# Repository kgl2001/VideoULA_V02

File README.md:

# VideoULA V02 — BBC Micro Video ULA Replacement
## 64-pin Xilinx XC9572XL CPLD Version

This repository contains the hardware design and firmware for the VideoULA V02, a drop-in replacement for the VC2069 Video ULA (IC6) in the Acorn BBC Micro Model B and Master 128.

---

## Project Overview

The original BBC Micro Video ULA (IC6) is a custom ASIC that is no longer manufactured. Failed or missing ULAs result in a non-functional machine. This project provides a modern replacement using a CPLD and a small external SRAM for palette storage.

There are three hardware versions of this replacement, each in a separate repository:

| Version | CPLD | Macrocells | Tool | Repository |
|---|---|---|---|---|
| V01 | Xilinx XC9572XL-10-VQ44 | 72 | ISE 14.7 | [VideoULA_V01](https://github.com/kgl2001/VideoULA_V01) |
| **V02** | Xilinx XC9572XL-10-VQ64 | 72 | ISE 14.7 | This repo |
| V03 | Atmel ATF1504AS-10AU44 | 64 | Quartus 13.0 SP1 | [VideoULA_V03](https://github.com/kgl2001/VideoULA_V03) |

All three versions share the same 28-pin DIP footprint as the original ULA and are pin-compatible with the BBC Micro motherboard.

---

## V02 Hardware

- **CPLD**: Xilinx XC9572XL-10-VQ64 (72 macrocells, 3.3V core, 5V tolerant I/O)
- **SRAM**: ISSI IS61LV256AL-10TLI (32K×8, 3.3V, TSOP-28, 10ns) — only locations 0-15 and bits 0-3 used
- **Oscillator**: 48MHz SMD oscillator (3225 package, 3.3V)
- **LDO**: XC6206P332MR (SOT-23, 3.3V) — powers CPLD core, oscillator and clock buffer
- **Clock buffer**: 74LV6T17 — buffers all 5 clock outputs (8/4/2/1MHz, CRTC) for Master 128 compatibility (5V powered); 6th channel buffers the 16MHz clock input
- **Power selection**: Solder bridge selects 3.3V or 5V for SRAM supply

### Key improvements over V01

- 64-pin CPLD package — more I/O pins available
- All clock outputs buffered via 74LV6T17 — improved compatibility with Master 128 custom ICs which require higher logic 1 voltage
- 3.3V SRAM option (IS61LV256AL-10TLI, 10ns) — faster and runs from 3.3V rail
- 3.3V oscillator — reduces CPLD input clamping current and heat
- 74LV6T17 used for both clock output buffering and 16MHz CLK_IN conditioning (Schmitt trigger)
- Separate CLK_16M and CLK_48M GCK pins — no solder bridge needed to switch modes, just reprogram
- SRAM_nWE pull-up to 3.3V — consistent with CPLD drive level

### Hardware Revisions

| Revision | Status | Changes |
|---|---|---|
| Rev01 | PCB designed, not yet built or tested | Initial release, largely based on V01 Rev03 |
| Rev02 | PCB designed, not yet built or tested | Repositioned JTAG header |

Note: Neither revision has been built or tested. The V02 design incorporates all improvements identified during V01 testing.

---

## Firmware

The firmware is written in Verilog and built using Xilinx ISE 14.7. The same Verilog source file (`src/VideoULA.v`) is shared between V02 and V03.

### Operating Modes

Two firmware builds are required — one per operating mode. Both CLK_16M and CLK_48M are wired to dedicated GCK pins, so no solder bridge changes are needed to switch modes — simply reprogram the CPLD with the appropriate `.jed` file.

#### 48MHz Mode (recommended)
- Uses the onboard 48MHz oscillator as the master clock
- Generates all BBC clock outputs (8/4/2/1MHz, CRTC, 6MHz) internally
- Provides clean, phase-locked 6MHz output for the SAA5050 teletext chip (tD ≈ 20ns ✓)
- Works reliably on all machines from cold power-up
- Build: uncomment `` `define CLK_48MHZ `` in `VideoULA.v`

#### 16MHz Mode
- Uses the BBC motherboard's 16MHz clock as the master clock
- The 48MHz oscillator is optional in 16MHz mode:
  - **Not fitted**: BBC's existing 6MHz circuit drives the SAA5050 as normal
  - **Fitted**: CPLD generates clean phase-locked 6MHz output (connect via IC37 replacement board)
- Build: uncomment `` `define CLK_16MHZ `` in `VideoULA.v`

### ISE Fitter Settings (critical)

| Setting | Value | Notes |
|---|---|---|
| Implementation Template | **Optimise Speed** | Density causes timing failures at temperature |
| Macrocell Power | **Std** | Low Power prevents BBC from booting |
| Output Slew Rate | Fast | |
| Default Powerup Value | Low | |

### Build Instructions

1. Open Xilinx ISE 14.7
2. Create a new project targeting `XC9572XL-10-VQ64`
3. Add `src/VideoULA.v` and `src/VideoULA.ucf` to the project
4. Select the operating mode by uncommenting the appropriate `define` in `VideoULA.v`
5. Set fitter options as above
6. Run `Implement Design` to generate the `.jed` file
7. Program the CPLD using iMPACT or a compatible JTAG programmer

---

## SRAM Wiring

The external SRAM stores the 16-entry colour palette (4 bits per entry):

| SRAM Pin | Connection |
|---|---|
| A0-A3 | CPLD SRAM_ADDR[0:3] |
| A4-A14 | GND (tie low) |
| D0-D3 | CPLD SRAM_DATA[0:3] (bidirectional) |
| D4-D7 | Leave unconnected |
| /WE | CPLD SRAM_nWE |
| /OE | GND (always output enabled) |
| /CS | GND (always selected) |

---

## 6MHz Clock for Mode 7 (Teletext)

- **48MHz mode**: CLK_6M pin provides clean phase-locked 6MHz (tD ≈ 20ns ✓). Connect to SAA5050 via IC37 replacement board.
- **16MHz mode, oscillator fitted**: CLK_6M provides clean phase-locked 6MHz, self-correcting every 1µs. Connect via IC37 replacement board.
- **16MHz mode, oscillator not fitted**: CLK_6M output ignored. BBC motherboard's existing 6MHz circuit used as normal.

---

## PCB Design Notes

The PCB has been designed using KiCAD V10 as a 2-layer board. It can easily be changed to a 4-layer board with GND/Power planes on the inner layers if signal integrity is a concern.

### JLCPCB Fabrication

The board design includes a 5×5mm silkscreen box on the underside of the PCB. This is used by JLCPCB to position a QR code serial number. When ordering from JLCPCB:

- Select **Specify position** in the QR code / 2D barcode options during the ordering process
- If this option is not selected, JLCPCB will print the 5×5mm silkscreen box as-is and attempt to place the QR code at a different location of their choosing

If not using JLCPCB, the chosen fabricator will likely print the 5×5mm box as a plain white square on the PCB. To avoid this, remove the silkscreen box from the PCB design and regenerate the Gerber files before submitting.

### Assembly

A combined CPL (Component Placement List) and BOM (Bill of Materials) Excel file is included in the Gerbers folder. This can be used directly with the JLCPCB PCBA (PCB Assembly) service.

Note that the JLCPCB Economy PCBA process only assembles components on one side of the PCB. Select the **top side** for assembly — this leaves only the SRAM and its associated decoupling capacitor to be hand soldered to the underside of the board.

---

## Known Limitations

- **Xilinx XC9572XL is obsolete** — becoming harder to source. V03 uses the still-in-production ATF1504AS as an alternative.
- **SCART/HDMI adapter compatibility**: Some SCART→HDMI display adapters may show minor pixel artefacts with non-standard screen modes. RGBtoHDMI and direct CRT connections are not affected.

---

## Compatibility

Designed for BBC Micro Model B and Master 128. The buffered clock outputs via 74LV6T17 provide the higher logic 1 voltage required by some Master 128 custom ICs.

---

## Credits

- **Ken Lowe** — PCB design, Verilog development and testing
- **hoglet (Stardot forums)** — Clock architecture analysis, DRAM timing analysis, community testing
- **Stardot community** — Testing, feedback and suggestions

---

## Licence

Hardware: [Creative Commons BY-SA 4.0](https://creativecommons.org/licenses/by-sa/4.0/)

Firmware: [MIT Licence](https://opensource.org/licenses/MIT)

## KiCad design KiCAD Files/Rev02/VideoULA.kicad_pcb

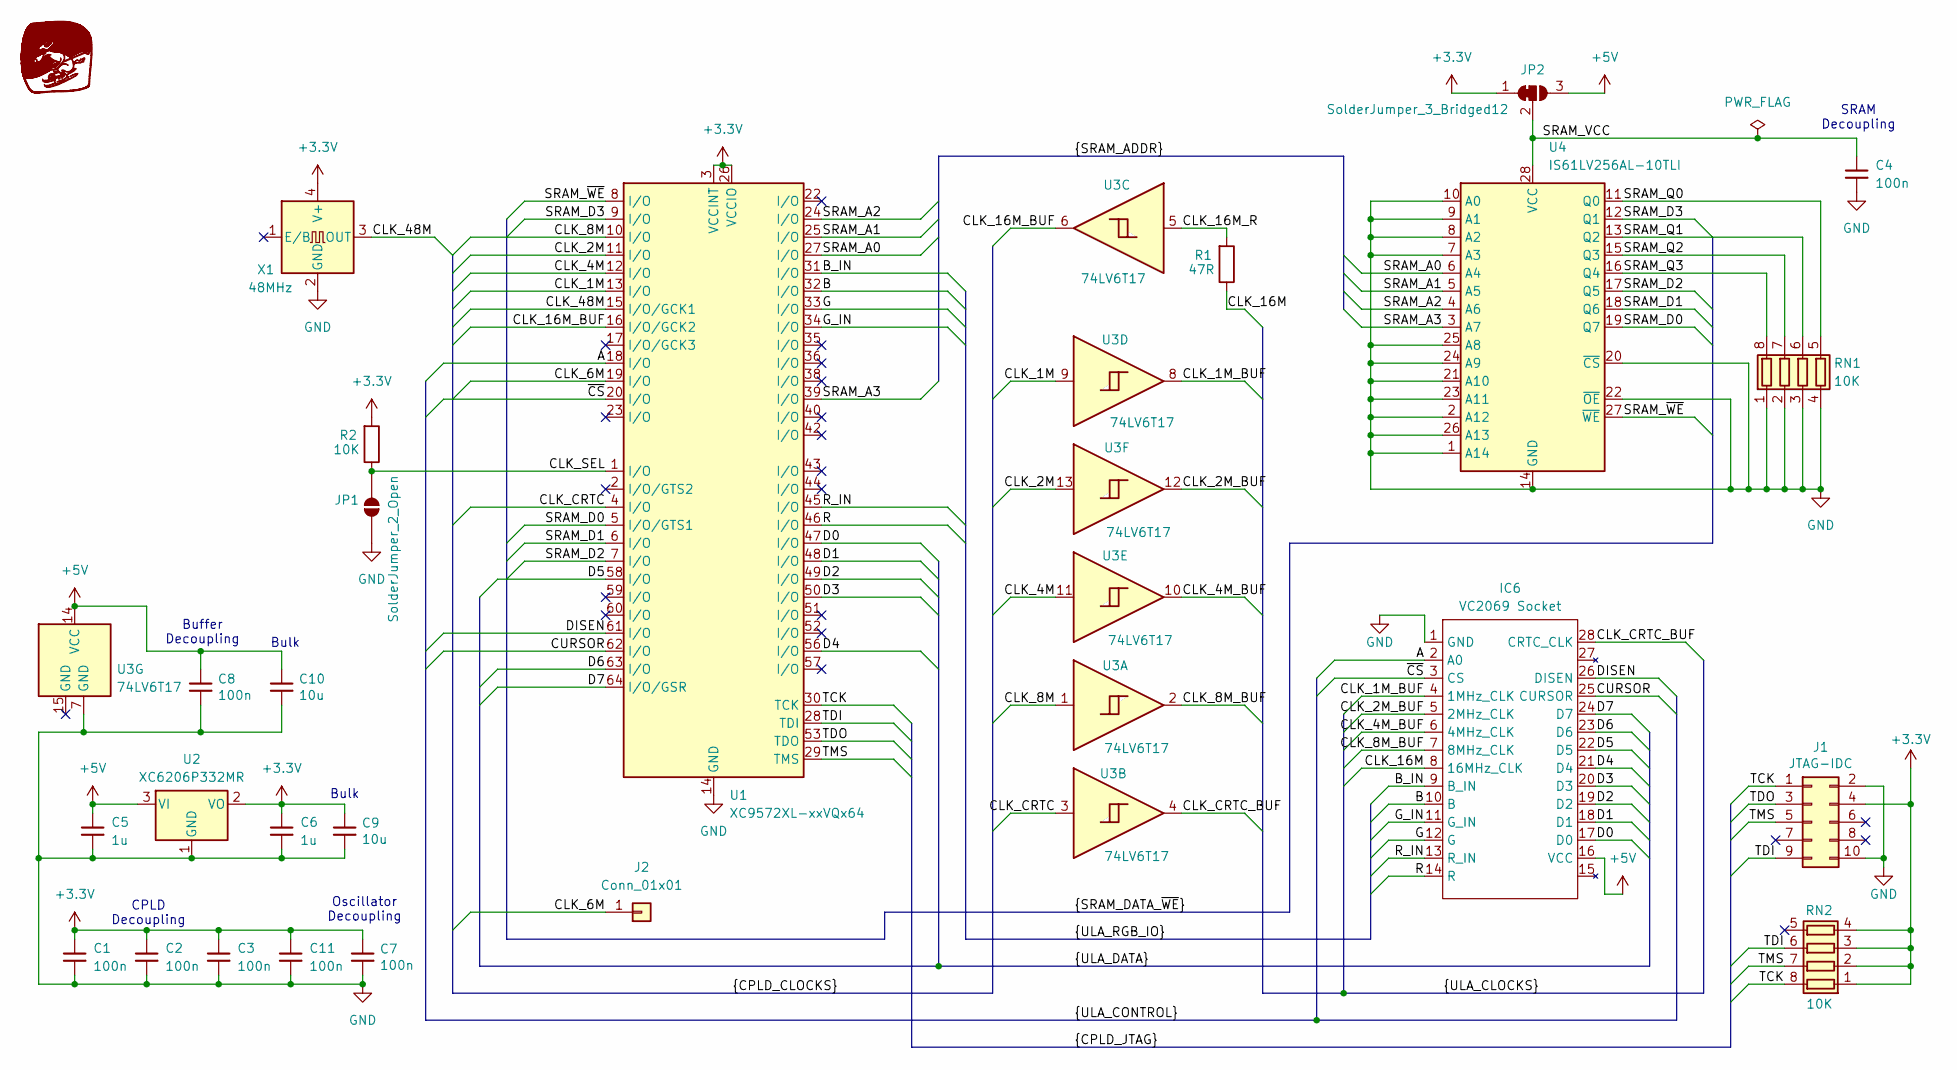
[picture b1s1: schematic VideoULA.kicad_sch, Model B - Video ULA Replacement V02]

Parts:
C1, C2, C3, C4, C7, C8, C11: 100n; C_0603_1608Metric; JLC Part Number C14663
C5, C6: 1u; C_0603_1608Metric; JLC Part Number C15849
C9, C10: 10u; C_0603_1608Metric; JLC Part Number C19702
G1: Skidog; skidog_inv
IC6: VC2069 Socket; DIP-28_W15.24mm
J1: JTAG-IDC; PinHeader_2x05_P2.54mm_Vertical
J2: Conn_01x01; PinHeader_1x01_P2.54mm_Horizontal
JP1: SolderJumper_2_Open; SolderJumper-2_P1.3mm_Open_RoundedPad1.0x1.5mm
JP2: SolderJumper_3_Bridged12; SolderJumper-3_P1.3mm_Bridged12_RoundedPad1.0x1.5mm
R1: 47R; R_0603_1608Metric; JLC Part Number C23182
R2: 10K; R_0603_1608Metric
RN1, RN2: 10K; R_Array_Convex_4x0603; JLC Part Number C29718
U1: XC9572XL-xxVQx64; TQFP-64_10x10mm_P0.5mm; JLC Part Number C90569
U2: XC6206P332MR; SOT-23-3; JLC Part Number C5446
U3: 74LV6T17; DHWQFN-14-1EP_2.5x3mm_P0.5mm_EP1x1.5mm_ThermalVias; JLC Part Number C22428345
U4: IS61LV256AL-10TLI; TSOP-I-28_11.8x8mm_P0.55mm_SRAM; JLC Part Number C2062662
X1: 48MHz; Oscillator_SMD_Yajingxin_TFOM48M4RHKCNT2T-4Pin_3.2x2.5mm; JLC Part Number C454614

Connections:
+3.3V: C1.1, C2.1, C3.1, C6.1, C7.1, C9.1, C11.1, J1.4, JP2.1 (A), R2.2, RN2.1 (R1.1), RN2.2 (R2.1), RN2.3 (R3.1), RN2.4 (R4.1), U1.3 (VCCINT), U1.26 (VCCIO), U1.37 (VCCINT), U1.55 (VCCIO), U2.2 (VO), X1.4 (V+)
+5V: C5.1, C8.1, C10.1, IC6.16 (VCC), JP2.3 (B), U2.3 (VI), U3.14 (VCC)
/A: IC6.2 (A0), U1.18 (I/O)
/B: IC6.10 (B), U1.32 (I/O)
/B_IN: IC6.9 (B_IN), U1.31 (I/O)
/CLK_1M: U1.13 (I/O), U3.9
/CLK_1M_BUF: IC6.4 (1MHz_CLK), U3.8
/CLK_2M: U1.11 (I/O), U3.13
/CLK_2M_BUF: IC6.5 (2MHz_CLK), U3.12
/CLK_4M: U1.12 (I/O), U3.11
/CLK_4M_BUF: IC6.6 (4MHz_CLK), U3.10
/CLK_6M: J2.1 (Pin_1_1), U1.19 (I/O)
/CLK_8M: U1.10 (I/O), U3.1
/CLK_8M_BUF: IC6.7 (8MHz_CLK), U3.2
/CLK_16M: IC6.8 (16MHz_CLK), R1.1
/CLK_16M_BUF: U1.16 (I/O/GCK2), U3.6
/CLK_16M_R: R1.2, U3.5
/CLK_48M: U1.15 (I/O/GCK1), X1.3 (OUT)
/CLK_CRTC: U1.4 (I/O), U3.3
/CLK_CRTC_BUF: IC6.28 (CRTC_CLK), U3.4
/CLK_SEL: JP1.2 (B), R2.1, U1.1 (I/O)
/CURSOR: IC6.25 (CURSOR), U1.62 (I/O)
/D0: IC6.17 (D0), U1.47 (I/O)
/D1: IC6.18 (D1), U1.48 (I/O)
/D2: IC6.19 (D2), U1.49 (I/O)
/D3: IC6.20 (D3), U1.50 (I/O)
/D4: IC6.21 (D4), U1.56 (I/O)
/D5: IC6.22 (D5), U1.58 (I/O)
/D6: IC6.23 (D6), U1.63 (I/O)
/D7: IC6.24 (D7), U1.64 (I/O/GSR)
/DISEN: IC6.26 (DISEN), U1.61 (I/O)
/G: IC6.12 (G), U1.33 (I/O)
/G_IN: IC6.11 (G_IN), U1.34 (I/O)
/R: IC6.14 (R), U1.46 (I/O)
/R_IN: IC6.13 (R_IN), U1.45 (I/O)
/SRAM_A0: U1.27 (I/O), U4.6 (A4)
/SRAM_A1: U1.25 (I/O), U4.5 (A5)
/SRAM_A2: U1.24 (I/O), U4.4 (A6)
/SRAM_A3: U1.39 (I/O), U4.3 (A7)
/SRAM_D0: U1.5 (I/O/GTS1), U4.19 (Q7)
/SRAM_D1: U1.6 (I/O), U4.18 (Q6)
/SRAM_D2: U1.7 (I/O), U4.17 (Q5)
/SRAM_D3: U1.9 (I/O), U4.12 (Q1)
/SRAM_Q0: RN1.5 (R4.2), U4.11 (Q0)
/SRAM_Q1: RN1.6 (R3.2), U4.13 (Q2)
/SRAM_Q2: RN1.7 (R2.2), U4.15 (Q3)
/SRAM_Q3: RN1.8 (R1.2), U4.16 (Q4)
/SRAM_VCC: C4.1, JP2.2 (C), U4.28 (VCC)
/SRAM_~WE: U1.8 (I/O), U4.27 (~WE)
/TCK: J1.1, RN2.8 (R1.2), U1.30 (TCK)
/TDI: J1.9, RN2.6 (R3.2), U1.28 (TDI)
/TDO: J1.3, U1.53 (TDO)
/TMS: J1.5, RN2.7 (R2.2), U1.29 (TMS)
/~CS: IC6.3 (CS), U1.20 (I/O)
GND: C1.2, C2.2, C3.2, C4.2, C5.2, C6.2, C7.2, C8.2, C9.2, C10.2, C11.2, IC6.1 (GND), J1.2, J1.10, JP1.1 (A), RN1.1 (R1.1), RN1.2 (R2.1), RN1.3 (R3.1), RN1.4 (R4.1), U1.14 (GND), U1.21 (GND), U1.41 (GND), U1.54 (GND), U2.1 (GND), U3.7 (GND), U4.1 (A14), U4.2 (A12), U4.7 (A3), U4.8 (A2), U4.9 (A1), U4.10 (A0), U4.14 (GND), U4.20 (~CS), U4.21 (A10), U4.22 (~OE), U4.23 (A11), U4.24 (A9), U4.25 (A8), U4.26 (A13), X1.2 (GND)

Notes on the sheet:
SRAM Decoupling
Oscillator Decoupling
CPLD Decoupling
Bulk
Buffer Decoupling

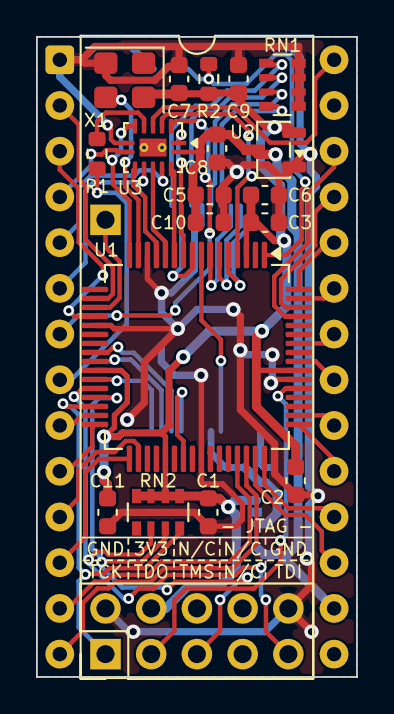
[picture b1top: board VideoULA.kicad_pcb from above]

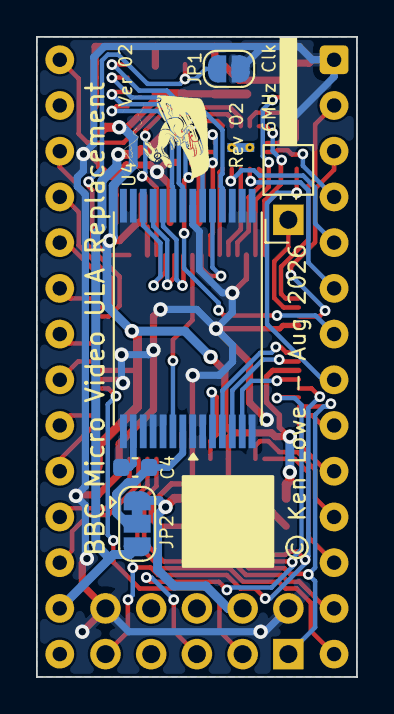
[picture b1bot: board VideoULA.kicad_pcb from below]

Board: 2 copper layers, 17.8 x 35.6 mm, 26 parts (6 on the bottom side), 55 nets.

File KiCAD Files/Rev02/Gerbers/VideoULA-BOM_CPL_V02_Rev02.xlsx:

Designator | Val | Package | Mid X | Mid Y | Rotation | Layer | JLC Part Number
C4 | 100n | C_0603_1608Metric | 89.034931999999998 | -62.523147999999999 | 0 | bottom | C14663
U4 | IS61LV256AL-10TLI | TSOP-I-28_11.8x8mm_P0.55mm_SRAM | 86.111000000000004 | -54.249400000000001 | 90 | bottom | C2062662
C1 | 100n | C_0603_1608Metric | 86.233366000000004 | -65.013999999999996 | -90 | top | C14663
C2 | 100n | C_0603_1608Metric | 91.089731999999998 | -63.266348000000001 | -90 | top | C14663
C3 | 100n | C_0603_1608Metric | 89.379599999999996 | -48.915399999999998 | 0 | top | C14663
C5 | 1u | C_0603_1608Metric | 86.3142 | -47.391399999999997 | 0 | top | C15849
C6 | 1u | C_0603_1608Metric | 89.379599999999996 | -47.391399999999997 | 0 | top | C15849
C7 | 100n | C_0603_1608Metric | 84.612399999999994 | -40.939799999999998 | 90 | top | C14663
C8 | 100n | C_0603_1608Metric | 86.7196 | -44.800600000000003 | -90 | top | C14663
C9 | 10u | C_0603_1608Metric | 87.912400000000005 | -40.939799999999998 | 90 | top | C19702
C10 | 10u | C_0603_1608Metric | 86.3142 | -48.915399999999998 | 0 | top | C19702
C11 | 100n | C_0603_1608Metric | 80.640853000000007 | -65.013999999999996 | -90 | top | C14663
R1 | 47R | R_0603_1608Metric | 80.0578 | -45.105400000000003 | 90 | top | C23182
R2 | 10K | R_0603_1608Metric | 86.2624 | -40.939799999999998 | -90 | top | C25804
RN1 | 10K | R_Array_Convex_4x0603 | 90.355732000000003 | -41.263348000000001 | -90 | top | C29718
RN2 | 10K | R_Array_Convex_4x0603 | 83.445766000000006 | -65.013999999999996 | 0 | top | C29718
U1 | XC9572XL-xxVQx64 | TQFP-64_10x10mm_P0.5mm | 85.602999999999994 | -56.383000000000003 | 180 | top | C90569
U2 | XC6206P332MR | SOT-23-3 | 89.862200000000001 | -44.876800000000003 | 0 | top | C5446
U3 | 74LV6T17 | DHWQFN-14-1EP_2.5x3mm_P0.5mm_EP1x1.5mm_ThermalVias | 83.164599999999993 | -44.7498 | -90 | top | C22428345
X1 | 48MHz | Oscillator_SMD_Yajingxin_TFOM48M4RHKCNT2T-4Pin_3.2x2.5mm | 81.592731999999998 | -41.009348000000003 | 180 | top | C454614

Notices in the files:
KiCAD Files/Rev02/VideoULA.kicad_pcb:
© Ken Lowe - Aug 2026
